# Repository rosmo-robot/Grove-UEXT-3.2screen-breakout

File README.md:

# Crowtail stand for ESP32 TFT Touch with Camera (ILI9341), 

A WIP breakout for [Makerfabs Esp32 with screen](https://www.makerfabs.com/esp32-3-2-inch-tft-touch-with-camera.html) Can be viewed in [Kicanvas](https://kicanvas.org/?repo=https%3A%2F%2Fgithub.com%2Frosmo-robot%2FGrove-UEXT-3.2screen-breakout%2Ftree%2Fmain%2FKicad)

Status: Early WIP draft

Built for the [open hardware electronics starter kit](https://github.com/rosmo-robot/robotics-resources/blob/main/guides/open-electronics/starter-kit.md)

## Mechanical
- 38.1 x 71 mm, 2 layers. Width equals the 15-pin header (15 x 2.54 mm).
- Right-angle 15-pin male header on the north edge, legs pointing off the edge into J1. Board lies flat behind the upright main board.
- Pin 1 (3V3) is on the LEFT, viewed from above with the header edge at the top. Match the labels on J1 before powering.
- Ports in two columns, pin rows vertical: J2 to J4 down the left edge, J5 to J9 down the right edge.

## Ports (see netlist.csv)
| Left | Crowtail module | GPIO | J1 pin | Right | Crowtail module | GPIO | J1 pin |
|---|---|---|---|---|---|---|---|
| J2 LIGHT | Light Sensor 2.0 | IO36 | 3 | J5 I2C | none in the kit | IO27 SCL, IO26 SDA | 14, 15 |
| J3 POT | Rotary Angle Sensor 2.0 | IO39 | 4 | J6 DHT11 | Temperature & Humidity 2.0 | IO18 | 12 |
| J4 STICK | RGB-LED (4x WS2812B) | IO32 | 6 | J7 BUZZER | Buzzer 2.0 | IO19 | 11 |
| | | | | J8 RELAY | Solid-State Relay 2.0 | IO23 | 9 |
| | | | | J9 BUTTON | Button 2.0 | IO25 | 8 |

J5 shares IO26 and IO27 with the on-board touch controller. Any I2C module added there must not clash with its address.

## UEXT 
2x5 male header [Olimex UEXT](https://www.olimex.com/Products/Modules/UEXT/)

| UEXT pin | Signal | GPIO | J1 pin | Shared with |
|---|---|---|---|---|
| 1 | 3V3 | n/a | 1 | all ports |
| 2 | GND | n/a | 2 | GND pour |
| 3 | TXD | IO22 | 7 | none |
| 4 | RXD | IO35 | 5 | none  |
| 5 | SCL | IO27 | 14 | J5 I2C |
| 6 | SDA | IO26 | 15 | J5 I2C |
| 7 | MISO | IO19 | 11 | J7 BUZZER |
| 8 | MOSI | IO23 | 9 | J8 RELAY |
| 9 | SCK | IO18 | 12 | J6 DHT11 |
| 10 | SSEL | IO5 | 13 | none  |

- Use UEXT or the shared Crowtail ports, not both at once.

## Electrical
- All ports 3V3 only. J1 has no 5 V.
- SIG2 is not connected except on I2C. IO21 is not connected. IO35, IO22, IO5 go to UEXT only.
- Signals on F.Cu. 3V3 on B.Cu (bus and two vertical spines). GND is a B.Cu pour.
- C1 10 uF and C2 100 nF sit near the header. I2C pull-ups are already on the main board.
- Remove the camera: the same GPIOs drive the camera bus.
- GPIO used by the main board and not available here: 12, 13, 14 (TFT and SD SPI), 15 (TFT CS), 33 (TFT DC), 4 (SD CS), 0 (touch interrupt), 1 and 3 (USB serial).

## Module notes at 3.3 V
- RGB-LED: rated 5 V. At 3.3 V it is below the WS2812B datasheet minimum supply (3.5 V). Run at low brightness and test colour accuracy.
- Solid-State Relay 2.0: Elecrow lists 3.3 V and 5 V control levels. Supply at 3.3 V is not verified. Output is rated 240 VAC / 4 A, DC switching not verified. Do not use the standard Crowtail Relay 2.0, which needs 5 V control.
- Other modules (Light, Rotary Angle, Temperature & Humidity, Buzzer, Button): not verified at 3.3 V.

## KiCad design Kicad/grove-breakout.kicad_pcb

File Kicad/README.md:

# Grove stand for ESP32 TFT Touch with Camera (ILI9341), J1

Status: draft v3, generated by script. Not opened in KiCad. Checked in Python only: header-to-GPIO map against the Makerfabs V1.1 schematic, copper clearance >= 0.2 mm, copper to edge >= 0.3 mm, every net connected (GND via the B.Cu pour).

## Mechanical
- 38.1 x 71 mm, 2 layers. Width equals the 15-pin header (15 x 2.54 mm).
- Right-angle 15-pin male header on the north edge, legs pointing off the edge into J1. Board lies flat behind the upright main board.
- Pin 1 (3V3) is on the LEFT, viewed from above with the header edge at the top. Match the labels on J1 before powering.
- Ports in two columns, pin rows vertical: J2 to J4 down the left edge, J5 to J9 down the right edge.

## Ports (see netlist.csv)
| Left | GPIO | J1 pin | Right | GPIO | J1 pin |
|---|---|---|---|---|---|
| J2 LIGHT | IO36 | 3 | J5 I2C | IO27 SCL, IO26 SDA | 14, 15 |
| J3 POT | IO39 | 4 | J6 DHT11 | IO18 | 12 |
| J4 STICK | IO32 | 6 | J7 BUZZER | IO19 | 11 |
| | | | J8 RELAY | IO23 | 9 |
| | | | J9 BUTTON | IO25 | 8 |

Right-hand order is fixed by routing: top to bottom must follow descending header position, or signals cross on one layer. J5 to J9 are renumbered from v1 (BUTTON was J5); the schematic refs are updated to match.

## UEXT (J10, placed, NOT routed)
2x5 male header, bottom of the board, pin 1 square (Olimex UEXT rev B host pinout). Pads already carry nets, so KiCad shows a ratsnest. Route it yourself.

| UEXT pin | Signal | GPIO | J1 pin | Shared with |
|---|---|---|---|---|
| 1 | 3V3 | n/a | 1 | all ports |
| 2 | GND | n/a | 2 | GND pour |
| 3 | TXD | IO22 | 7 | none (new net UEXT_TXD_IO22) |
| 4 | RXD | IO35 | 5 | none (new net UEXT_RXD_IO35) |
| 5 | SCL | IO27 | 14 | J5 I2C |
| 6 | SDA | IO26 | 15 | J5 I2C |
| 7 | MISO | IO19 | 11 | J7 BUZZER |
| 8 | MOSI | IO23 | 9 | J8 RELAY |
| 9 | SCK | IO18 | 12 | J6 DHT11 |
| 10 | SSEL | IO5 | 13 | none (new net UEXT_SSEL_IO5) |

- Use UEXT or the shared Grove ports, not both at once.
- IO35 is input-only (fine for RXD). IO5 is a strapping pin.
- Silkscreen format: signal, GPIO, #J1 pin, Grove port. Pins 5,7,13 of J1 now carry nets (were NC).

## Electrical
- All ports 3V3 only. J1 has no 5 V.
- SIG2 is not connected except on I2C. IO21 is not connected. IO35, IO22, IO5 go to UEXT only.
- Signals on F.Cu. 3V3 on B.Cu (bus and two vertical spines). GND is a B.Cu pour.
- C1 10 uF and C2 100 nF sit near the header. I2C pull-ups are already on the main board.
- Unplug the camera FPC: the same GPIOs drive the camera bus.

## Check before ordering
- Zone: press B in KiCad to refill GND.
- Footprints are written inline with library names. Confirm the right-angle header leg length reaches into J1.
- Connectors are JST PH 4-pin 2.00 mm. Not verified to mate with your Grove cables.
- Reference and value text is hidden on the footprints. Port names are board silkscreen.
- Not verified: Grove relay and RGB stick at 3.3 V.

## Schematic
- v1 bug fixed: Grove port net labels sat 1.27 mm off the pin ends, so the ports were not connected in the schematic. Now on the pin ends; every pin has a label or no-connect.
- J10 UEXT added with the same nets.

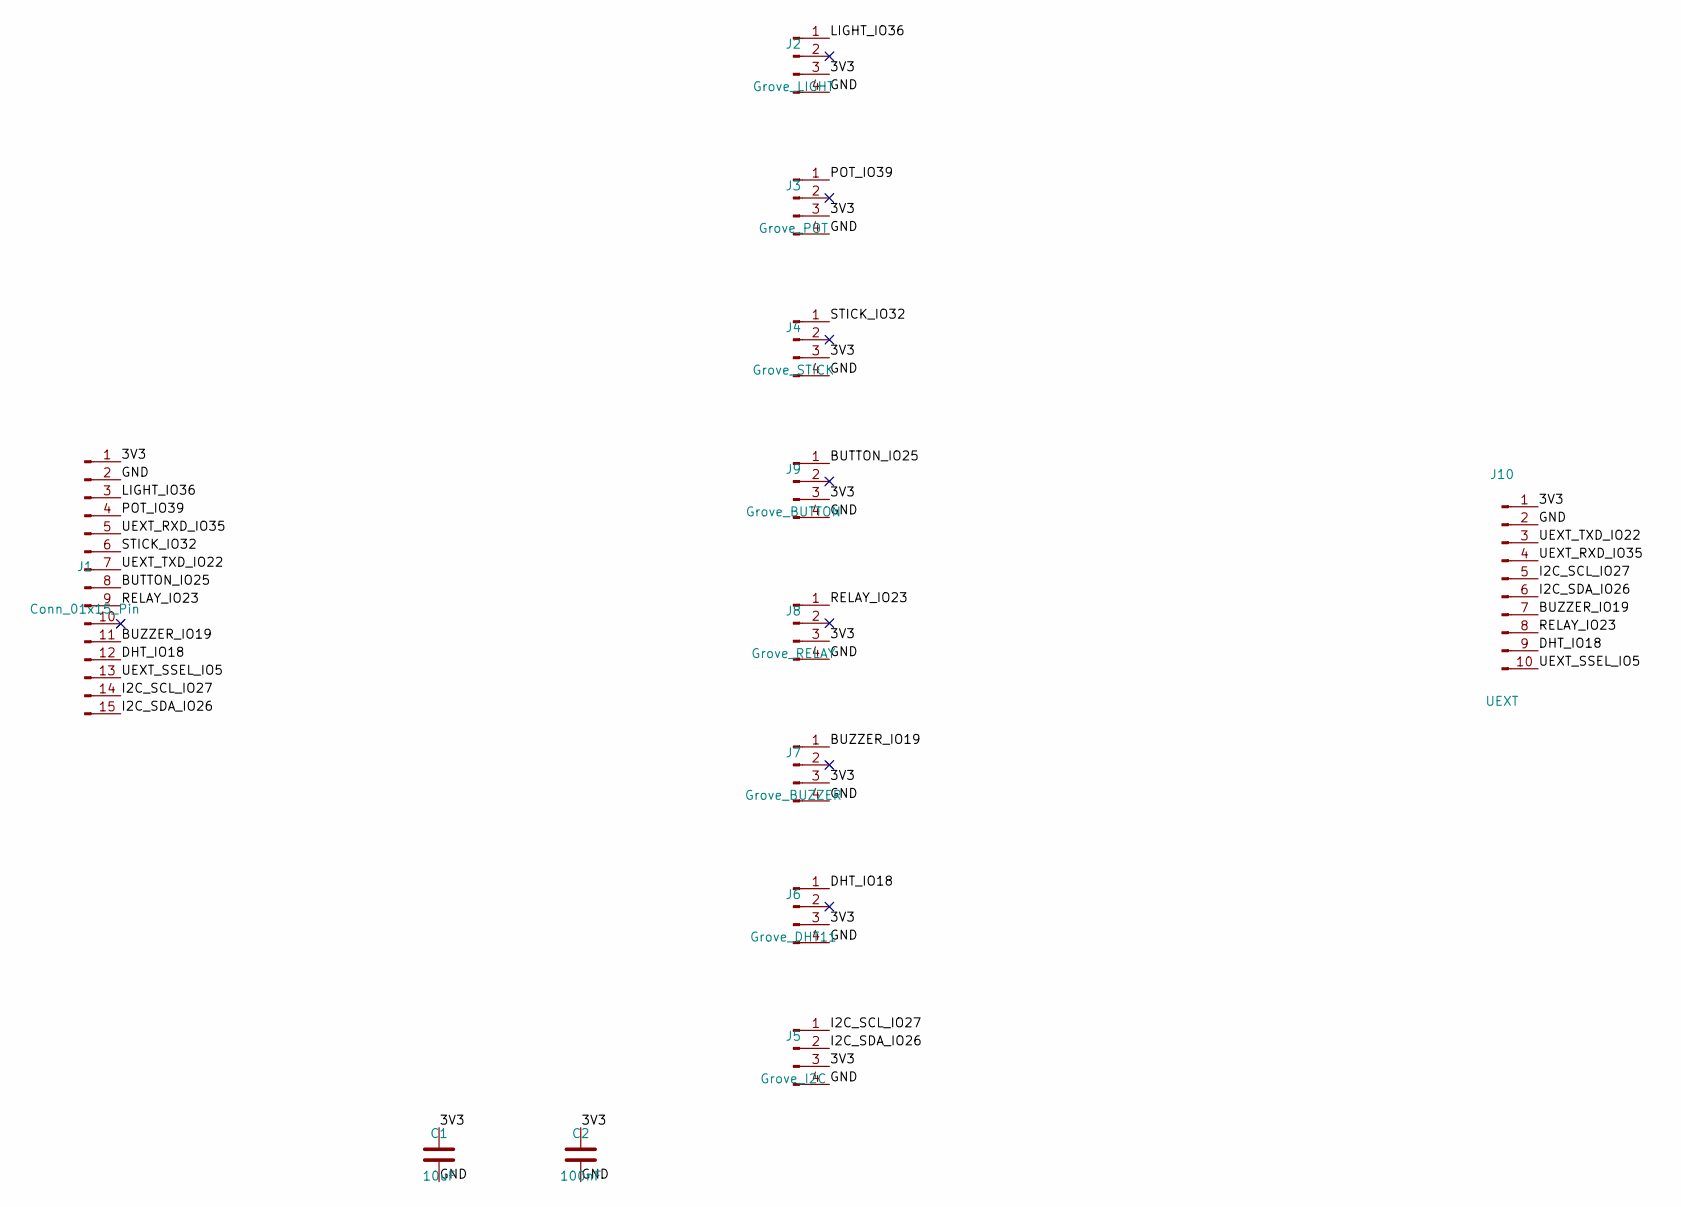
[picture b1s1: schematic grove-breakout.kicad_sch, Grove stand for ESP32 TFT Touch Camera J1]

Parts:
C1: 10uF; C_0805_2012Metric
C2: 100nF; C_0603_1608Metric
J1: Conn_01x15_Pin; PinHeader_1x15_P2.54mm_Horizontal
J2: Grove_LIGHT; JST_PH_B4B-PH-K_1x04_P2.00mm_Vertical
J3: Grove_POT; JST_PH_B4B-PH-K_1x04_P2.00mm_Vertical
J4: Grove_STICK; JST_PH_B4B-PH-K_1x04_P2.00mm_Vertical
J5: Grove_I2C; JST_PH_B4B-PH-K_1x04_P2.00mm_Vertical
J6: Grove_DHT11; JST_PH_B4B-PH-K_1x04_P2.00mm_Vertical
J7: Grove_BUZZER; JST_PH_B4B-PH-K_1x04_P2.00mm_Vertical
J8: Grove_RELAY; JST_PH_B4B-PH-K_1x04_P2.00mm_Vertical
J9: Grove_BUTTON; JST_PH_B4B-PH-K_1x04_P2.00mm_Vertical
J10: UEXT; PinHeader_2x05_P2.54mm_Vertical

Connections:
3V3: C1.1, C2.1, J1.1, J2.3, J3.3, J4.3, J5.3, J6.3, J7.3, J8.3, J9.3, J10.1; also elsewhere on the board
BUTTON_IO25: J1.8, J9.1
BUZZER_IO19: J1.11, J7.1, J10.7
DHT_IO18: J1.12, J6.1, J10.9
GND: C1.2, C2.2, J1.2, J2.4, J3.4, J4.4, J5.4, J6.4, J7.4, J8.4, J9.4, J10.2; also elsewhere on the board
I2C_SCL_IO27: J1.14, J5.1, J10.5; also elsewhere on the board
I2C_SDA_IO26: J1.15, J5.2, J10.6; also elsewhere on the board
LIGHT_IO36: J1.3, J2.1
POT_IO39: J1.4, J3.1
RELAY_IO23: J1.9, J8.1, J10.8
STICK_IO32: J1.6, J4.1
UEXT_RXD_IO35: J1.5, J10.4
UEXT_SSEL_IO5: J1.13, J10.10
UEXT_TXD_IO22: J1.7, J10.3

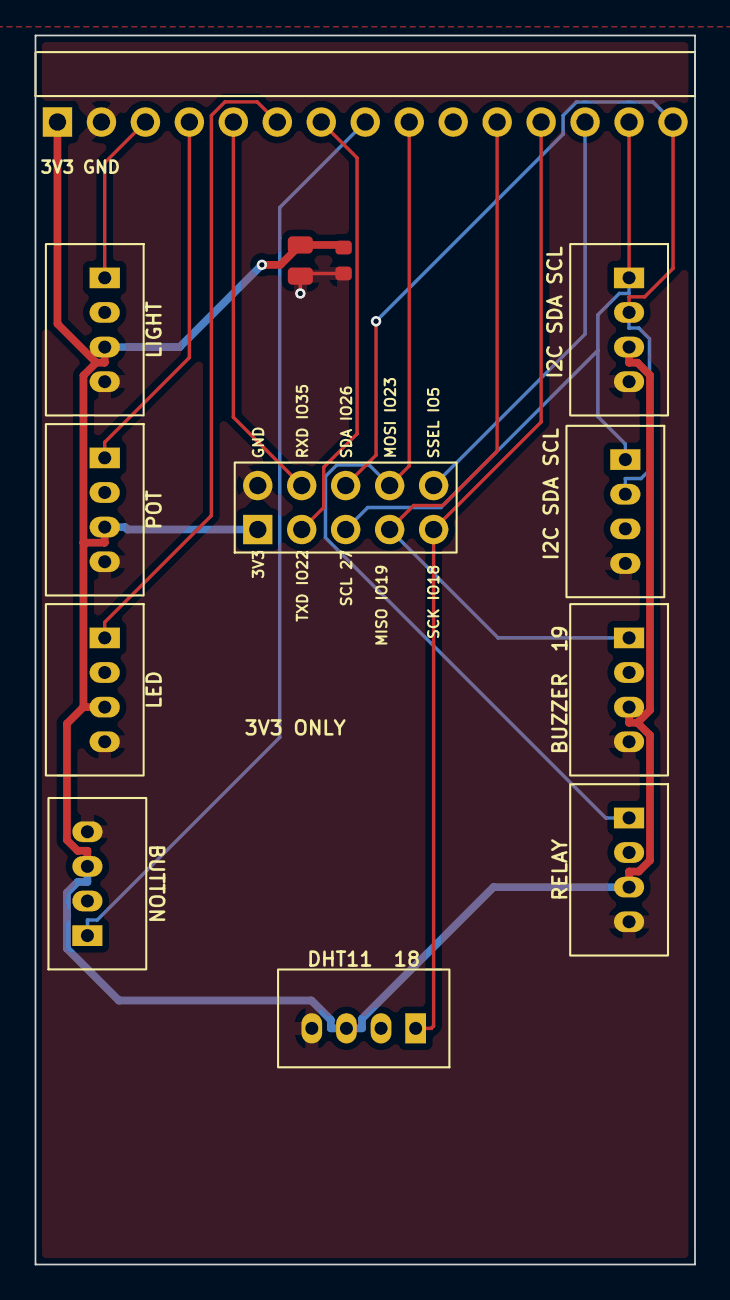
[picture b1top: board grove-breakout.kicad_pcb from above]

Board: 2 copper layers, 38.1 x 71.0 mm, 13 parts (0 on the bottom side), 14 nets.

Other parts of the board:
J5#2: Grove_I2C; JST_PH_B4B-PH-K_1x04_P2.00mm_Vertical

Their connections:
3V3: J5#2.3; also elsewhere on the board
GND: J5#2.4; also elsewhere on the board
I2C_SCL_IO27: J5#2.1; also elsewhere on the board
I2C_SDA_IO26: J5#2.2; also elsewhere on the board

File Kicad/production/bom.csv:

Designator,Footprint,Quantity,Value,LCSC Part #
C1,0805,1,10uF,
C2,0603,1,100nF,
J1,PinHeader_1x15_P2.54mm_Horizontal,1,Conn_01x15_Pin,
J10,PinHeader_2x05_P2.54mm_Vertical,1,UEXT,
J2,JST_PH_B4B-PH-K_1x04_P2.00mm_Vertical,1,Grove_LIGHT,
J3,JST_PH_B4B-PH-K_1x04_P2.00mm_Vertical,1,Grove_POT,
J4,JST_PH_B4B-PH-K_1x04_P2.00mm_Vertical,1,Grove_STICK,
"J5_2, J5",JST_PH_B4B-PH-K_1x04_P2.00mm_Vertical,2,Grove_I2C,
J6,JST_PH_B4B-PH-K_1x04_P2.00mm_Vertical,1,Grove_DHT11,
J7,JST_PH_B4B-PH-K_1x04_P2.00mm_Vertical,1,Grove_BUZZER,
J8,JST_PH_B4B-PH-K_1x04_P2.00mm_Vertical,1,Grove_RELAY,
J9,JST_PH_B4B-PH-K_1x04_P2.00mm_Vertical,1,Grove_BUTTON,
